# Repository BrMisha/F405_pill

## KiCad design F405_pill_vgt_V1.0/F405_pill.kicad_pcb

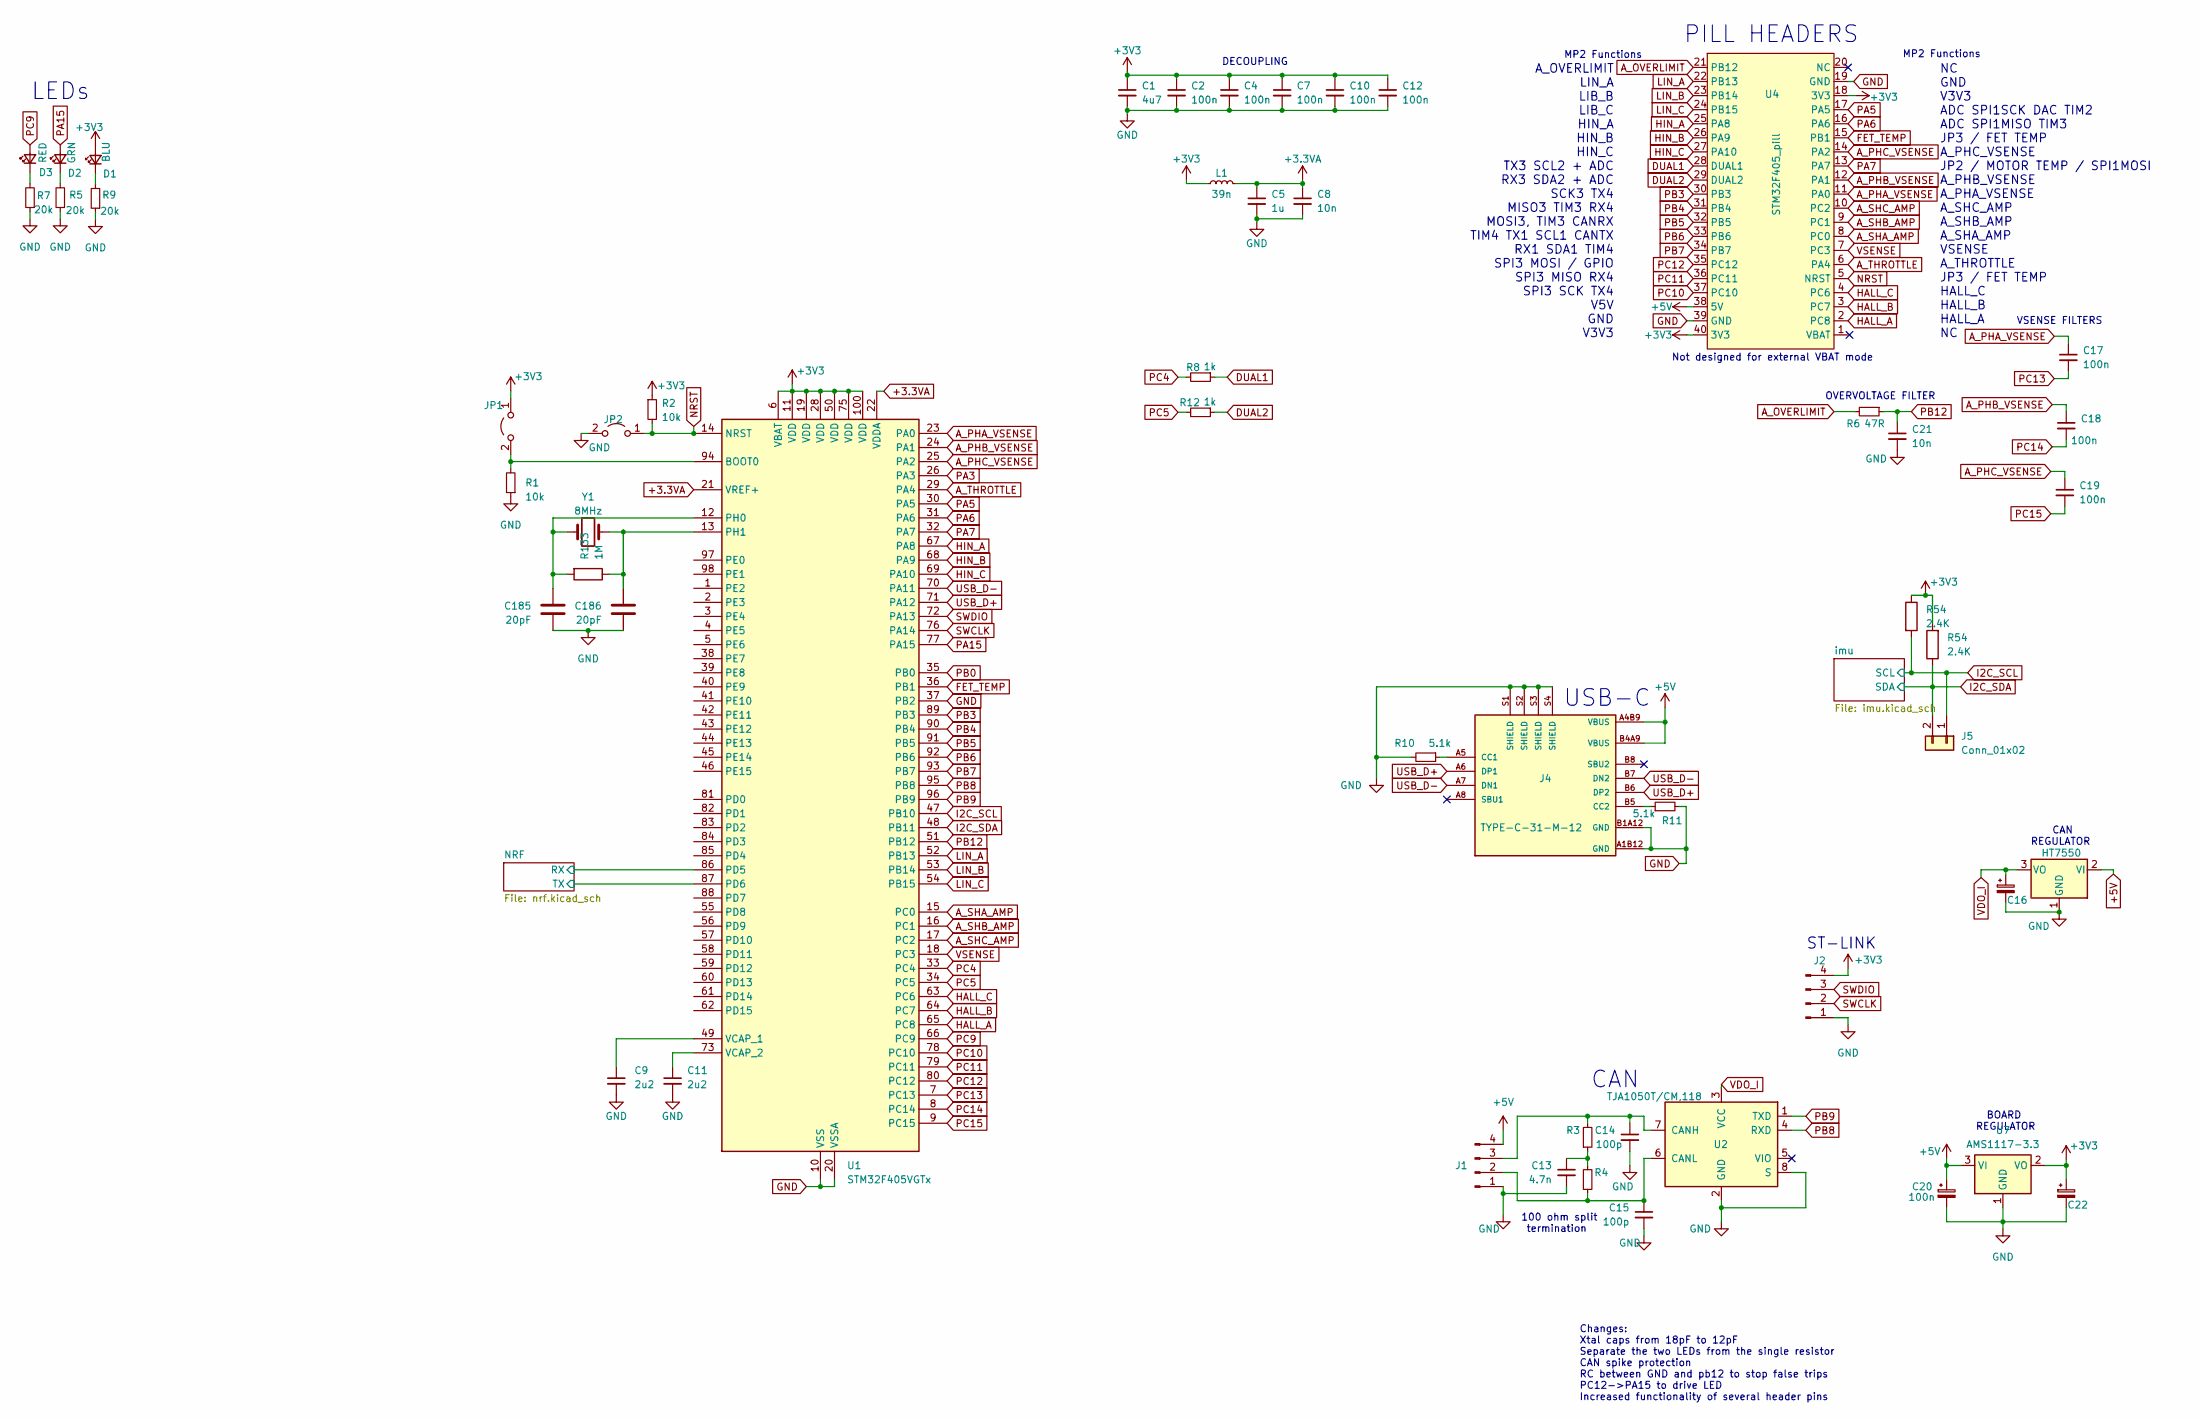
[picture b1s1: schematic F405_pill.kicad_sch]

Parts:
C1: 4u7; C_0402_1005Metric; LCSC C23733
C2, C4, C7, C10, C12, C17, C18, C19: 100n; C_0402_1005Metric; LCSC C1525
C5: 1u; C_0402_1005Metric; LCSC C52923
C8, C21: 10n; C_0402_1005Metric; LCSC C15195
C9, C11: 2u2; C_0603_1608Metric; LCSC C23630
C13: 4.7n; C_0402_1005Metric; LCSC C1538
C14, C15: 100p; C_0402_1005Metric; LCSC C1546
C16, C22: 10u; C_0603_1608Metric; LCSC C962635
C20: 100n; CP_EIA-3216-18_Kemet-A; LCSC C122257
C185, C186: 20pF; C_0402_1005Metric; MPN C1554
D1: BLU; LED_0603_1608Metric; LCSC C72041
D2: GRN; LED_0603_1608Metric; LCSC C72043
D3: RED; LED_0603_1608Metric; LCSC C2286
J1, J2: Conn_01x04_Male; my_4_pin
J4: TYPE-C-31-M-12; HRO_TYPE-C-31-M-12; PARTREV A; LCSC C165948
J5: Conn_01x02; PinHeader_1x02_P2.54mm_Vertical
JP1, JP2: Jumper_2_Open; my_2_pin
L1: 39n; L_0402_1005Metric; LCSC C26443
R1, R2: 10k; R_0402_1005Metric; LCSC C25744
R3, R4: 100Ω; R_0402_1005Metric; LCSC C25076
R5, R7, R9: 20k; R_0402_1005Metric; LCSC C25765
R6: 47R; R_0402_1005Metric; LCSC C25118
R8, R12: 1k; R_0402_1005Metric; LCSC C11702
R10, R11: 5.1k; R_0402_1005Metric; LCSC C25905
R54: 2.4K; R_0805_2012Metric; MPN C17526
R133: 1M; R_0402_1005Metric; MPN C26083
U1: STM32F405VGTx; LQFP-100_14x14mm_P0.5mm; LCSC C56621
U2: TJA1050T/CM,118; SOIC-8_3.9x4.9mm_P1.27mm; LCSC C6952
U4: STM32F405_pill
U5: HT7550; SOT-89-3; LCSC C16106
U7: AMS1117-3.3; SOT-223-3_TabPin2; MPN C6186
Y1: 8MHz; Crystal_SMD_5032-2Pin_5.0x3.2mm; MPN C115962

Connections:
+3.3VA: C5.1, C8.1, L1.2, U1.21 (VREF+), U1.22 (VDDA)
+3V3: C1.1, C2.1, C4.1, C7.1, C10.1, C12.1, C22.1, D1.2 (A), J2.4, JP1.1 (A), L1.1, R2.1, U1.6 (VBAT), U1.11 (VDD), U1.19 (VDD), U1.28 (VDD), U1.50 (VDD), U1.75 (VDD), U1.100 (VDD), U4.18 (3V3), U4.40 (3V3), U7.2 (VO); also elsewhere on the board
+5V: C20.1, J1.4, J4.A4B9 (VBUS), J4.B4A9 (VBUS), U4.38 (5V), U5.2 (VI), U7.3 (VI)
/NRF/RX: U1.86 (PD5); also elsewhere on the board
/NRF/TX: U1.87 (PD6); also elsewhere on the board
A_OVERLIMIT: R6.2, U4.21 (PB12)
A_PHA_VSENSE: C17.1, U1.23 (PA0), U4.11 (PA0)
A_PHB_VSENSE: C18.1, U1.24 (PA1), U4.12 (PA1)
A_PHC_VSENSE: C19.1, U1.25 (PA2), U4.14 (PA2)
A_SHA_AMP: U1.15 (PC0), U4.8 (PC0)
A_SHB_AMP: U1.16 (PC1), U4.9 (PC1)
A_SHC_AMP: U1.17 (PC2), U4.10 (PC2)
A_THROTTLE: U1.29 (PA4), U4.6 (PA4)
DUAL1: R8.1, U4.28 (DUAL1)
DUAL2: R12.1, U4.29 (DUAL2)
FET_TEMP: U1.36 (PB1), U4.15 (PB1)
GND: C1.2, C2.2, C4.2, C5.2, C7.2, C8.2, C9.2, C10.2, C11.2, C12.2, C13.2, C14.2, C15.2, C16.2, C20.2, C21.2, C22.2, J1.1, J2.1, J4.A1B12 (GND), J4.B1A12 (GND), J4.S1 (SHIELD), J4.S2 (SHIELD), J4.S3 (SHIELD), J4.S4 (SHIELD), JP2.2 (B), R1.1, R5.1, R7.1, R9.1, R10.2, R11.2, U1.10 (VSS), U1.20 (VSSA), U1.27 (VSS), U1.37 (PB2), U1.74 (VSS), U1.99 (VSS), U2.2 (GND), U2.8 (S), U4.19 (GND), U4.39 (GND), U5.1 (GND), U7.1 (GND); also elsewhere on the board
HALL_A: U1.65 (PC8), U4.2 (PC8)
HALL_B: U1.64 (PC7), U4.3 (PC7)
HALL_C: U1.63 (PC6), U4.4 (PC6)
HIN_A: U1.67 (PA8), U4.25 (PA8)
HIN_B: U1.68 (PA9), U4.26 (PA9)
HIN_C: U1.69 (PA10), U4.27 (PA10)
I2C_SCL: J5.1, U1.47 (PB10); also elsewhere on the board
I2C_SDA: J5.2, U1.48 (PB11); also elsewhere on the board
LIN_A: U1.52 (PB13), U4.22 (PB13)
LIN_B: U1.53 (PB14), U4.23 (PB14)
LIN_C: U1.54 (PB15), U4.24 (PB15)
NRST: JP2.1 (A), R2.2, U1.14 (NRST), U4.5 (NRST)
unnamed: C13.1, R3.1, R4.2
unnamed: D1.1 (K), R9.2
unnamed: D2.1 (K), R5.2
unnamed: D3.1 (K), R7.2
unnamed: C15.1, J1.2, R4.1, U2.6 (CANL)
unnamed: C14.1, J1.3, R3.2, U2.7 (CANH)
unnamed: J4.A5 (CC1), R10.1
unnamed: J4.B5 (CC2), R11.1
unnamed: JP1.2 (B), R1.2, U1.94 (BOOT0)
unnamed 41: U1.12 (PH0), Y1.1; also elsewhere on the board
unnamed 42: U1.13 (PH1), Y1.2; also elsewhere on the board
unnamed: C9.1, U1.49 (VCAP_1)
unnamed: C11.1, U1.73 (VCAP_2)
PA3: U1.26 (PA3)
PA5: U1.30 (PA5), U4.17 (PA5)
PA6: U1.31 (PA6), U4.16 (PA6)
PA7: U1.32 (PA7), U4.13 (PA7)
PA15: D2.2 (A), U1.77 (PA15)
PB0: U1.35 (PB0)
PB3: U1.89 (PB3), U4.30 (PB3)
PB4: U1.90 (PB4), U4.31 (PB4)
PB5: U1.91 (PB5), U4.32 (PB5)
PB6: U1.92 (PB6), U4.33 (PB6)
PB7: U1.93 (PB7), U4.34 (PB7)
PB8: U1.95 (PB8), U2.4 (RXD)
PB9: U1.96 (PB9), U2.1 (TXD)
PB12: C21.1, R6.1, U1.51 (PB12)
PC4: R8.2, U1.33 (PC4)
PC5: R12.2, U1.34 (PC5)
PC9: D3.2 (A), U1.66 (PC9)
PC10: U1.78 (PC10), U4.37 (PC10)
PC11: U1.79 (PC11), U4.36 (PC11)
PC12: U1.80 (PC12), U4.35 (PC12)
PC13: C17.2, U1.7 (PC13)
PC14: C18.2, U1.8 (PC14)
PC15: C19.2, U1.9 (PC15)
SWCLK: J2.2, U1.76 (PA14)
SWDIO: J2.3, U1.72 (PA13)
USB_D+: J4.A6 (DP1), J4.B6 (DP2), U1.71 (PA12)
USB_D-: J4.A7 (DN1), J4.B7 (DN2), U1.70 (PA11)
VDO_I: C16.1, U2.3 (VCC), U5.3 (VO)
VSENSE: U1.18 (PC3), U4.7 (PC3)

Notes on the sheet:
CAN
NC GND V3V3 ADC SPI1SCK DAC TIM2 ADC SPI1MISO TIM3 JP3 / FET TEMP A_PHC_VSENSE JP2 / MOTOR TEMP / SPI1MOSI A_PHB_VSENSE A_PHA_VSENSE A_SHC_AMP A_SHB_AMP A_SHA_AMP VSENSE A_THROTTLE JP3 / FET TEMP HALL_C HALL_B HALL_A NC
ST-LINK
Changes: Xtal caps from 18pF to 12pF Separate the two LEDs from the single resistor CAN spike protection RC between GND and pb12 to stop false trips PC12->PA15 to drive LED Increased functionality of several header pins
A_OVERLIMIT LIN_A LIB_B LIB_C HIN_A HIN_B HIN_C TX3 SCL2 + ADC RX3 SDA2 + ADC SCK3 TX4 MISO3 TIM3 RX4 MOSI3, TIM3 CANRX TIM4 TX1 SCL1 CANTX RX1 SDA1 TIM4 SPI3 MOSI / GPIO SPI3 MISO RX4 SPI3 SCK TX4 V5V GND V3V3
BOARD REGULATOR
PILL HEADERS
MP2 Functions
CAN REGULATOR
VSENSE FILTERS
OVERVOLTAGE FILTER
LEDs
USB-C
Not designed for external VBAT mode
DECOUPLING
100 ohm split termination

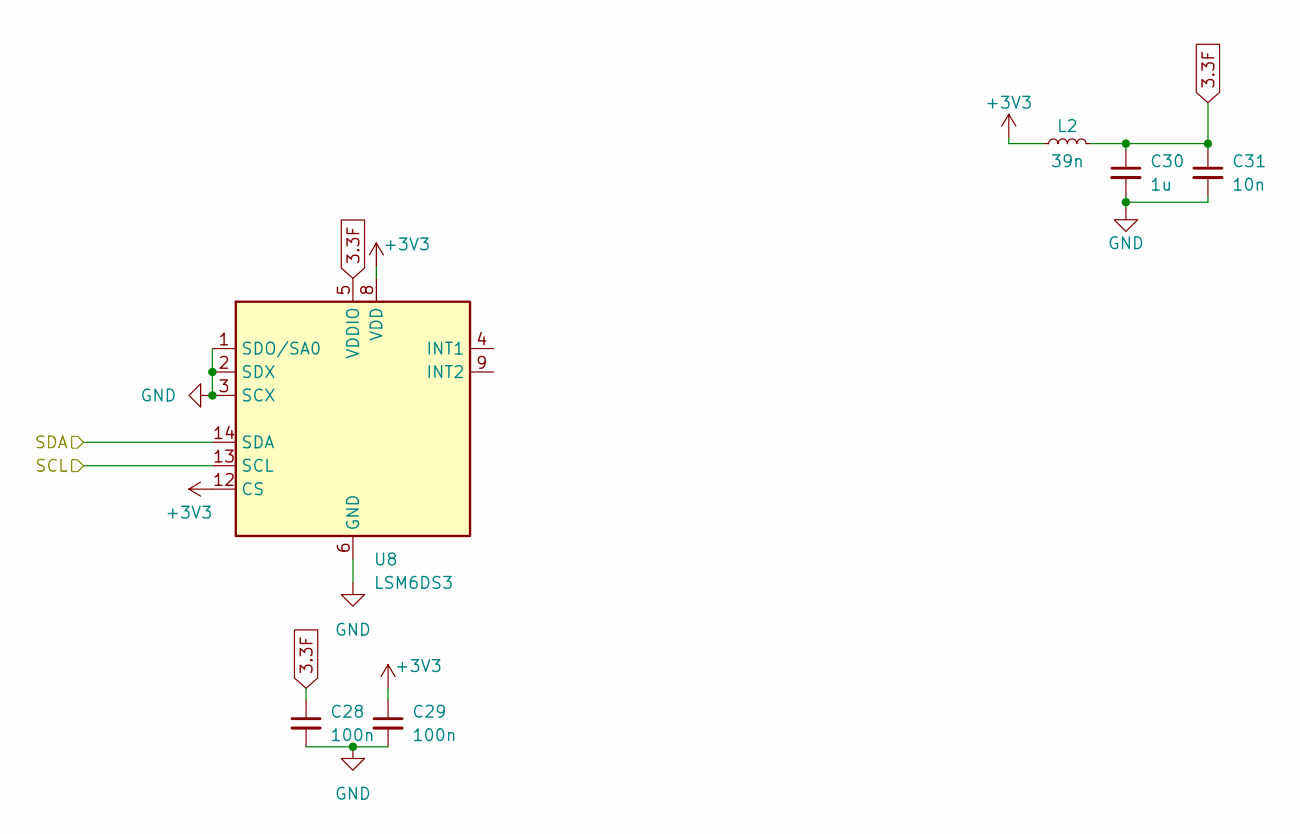
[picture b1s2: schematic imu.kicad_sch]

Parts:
C28, C29: 100n; C_0402_1005Metric; LCSC C1525
C30: 1u; C_0402_1005Metric; LCSC C52923
C31: 10n; C_0402_1005Metric; LCSC C15195
L2: 39n; L_0402_1005Metric; LCSC C26443
U8: LSM6DS3; LGA-14_3x2.5mm_P0.5mm_LayoutBorder3x4y; MPN C95230

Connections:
3.3F: C28.1, C30.1, C31.1, L2.2, U8.5 (VDDIO)
+3V3: C29.1, L2.1, U8.8 (VDD), U8.12 (CS); also elsewhere on the board
GND: C28.2, C29.2, C30.2, C31.2, U8.1 (SDO/SA0), U8.2 (SDX), U8.3 (SCX), U8.6 (GND), U8.7 (GND); also elsewhere on the board
I2C_SCL: U8.13 (SCL); also elsewhere on the board
I2C_SDA: U8.14 (SDA); also elsewhere on the board

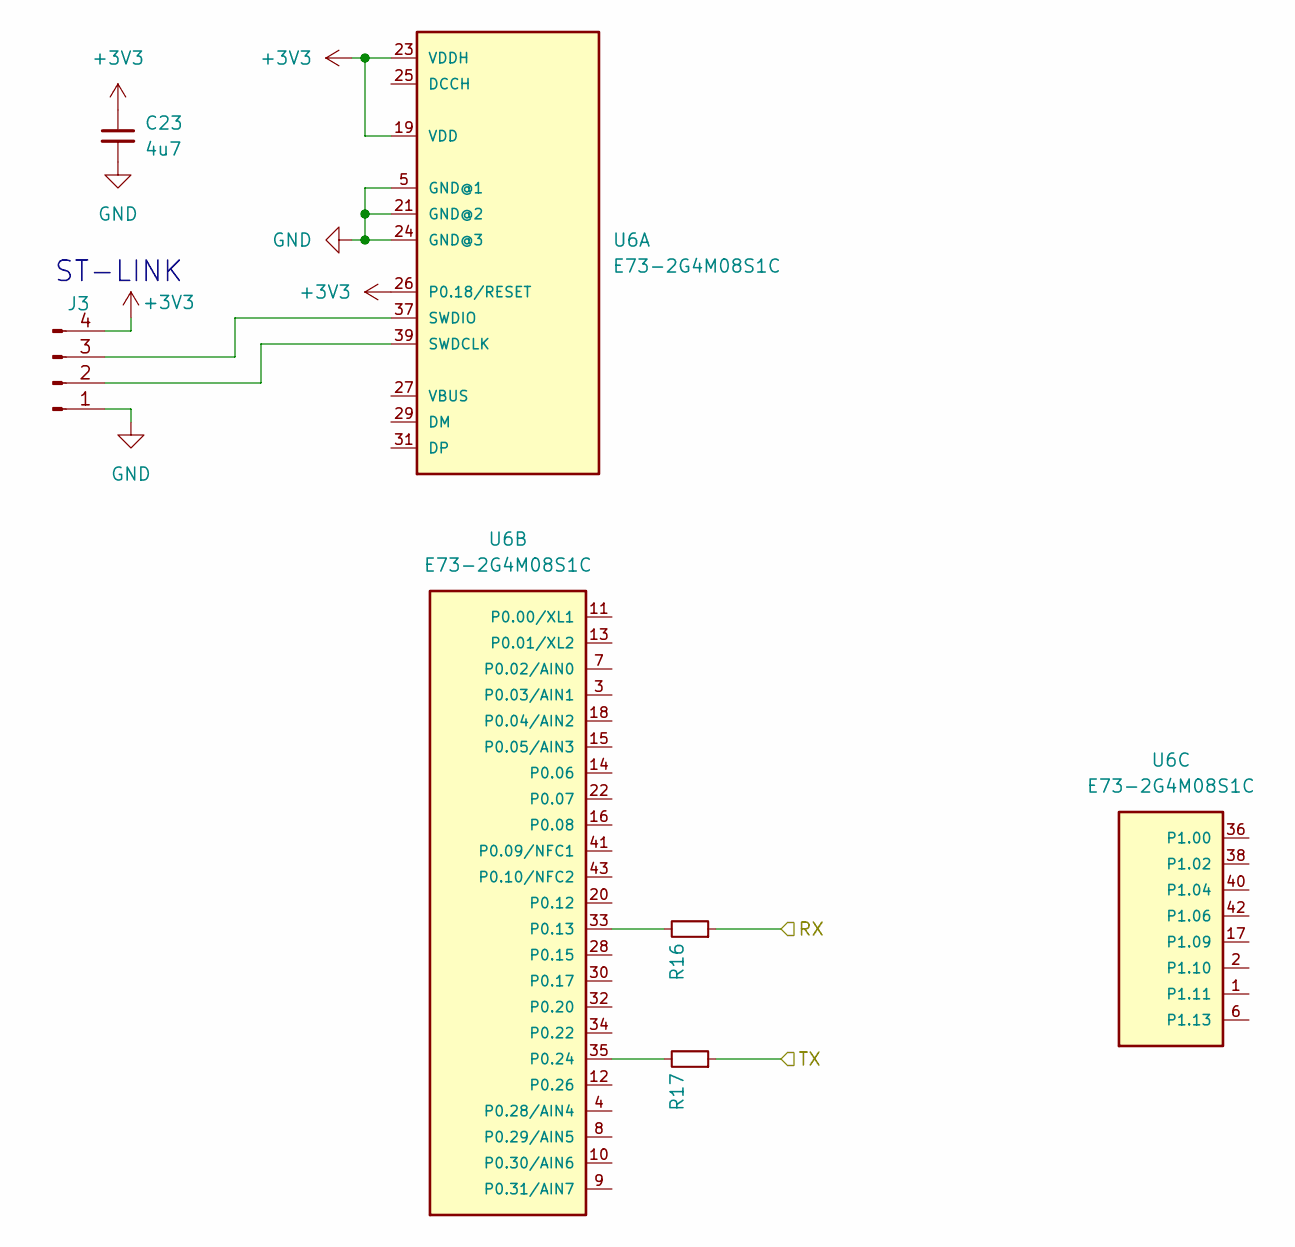
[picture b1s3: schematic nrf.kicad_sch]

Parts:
C23: 4u7; C_0402_1005Metric; LCSC C23733
J3: Conn_01x04_Male; PinHeader_1x04_P2.54mm_Vertical
R16, R17: 100Ω; R_0402_1005Metric; LCSC C25076
U6: E73-2G4M08S1C

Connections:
+3V3: C23.1, J3.4, U6.19 (VDD), U6.23 (VDDH), U6.26 (P0.18/RESET); also elsewhere on the board
/NRF/RX: R16.1; also elsewhere on the board
/NRF/TX: R17.1; also elsewhere on the board
GND: C23.2, J3.1, U6.5 (GND@1), U6.21 (GND@2), U6.24 (GND@3); also elsewhere on the board
unnamed: J3.2, U6.39 (SWDCLK)
unnamed: J3.3, U6.37 (SWDIO)
unnamed: R16.2, U6.33 (P0.13)
unnamed: R17.2, U6.35 (P0.24)

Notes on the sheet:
ST-LINK

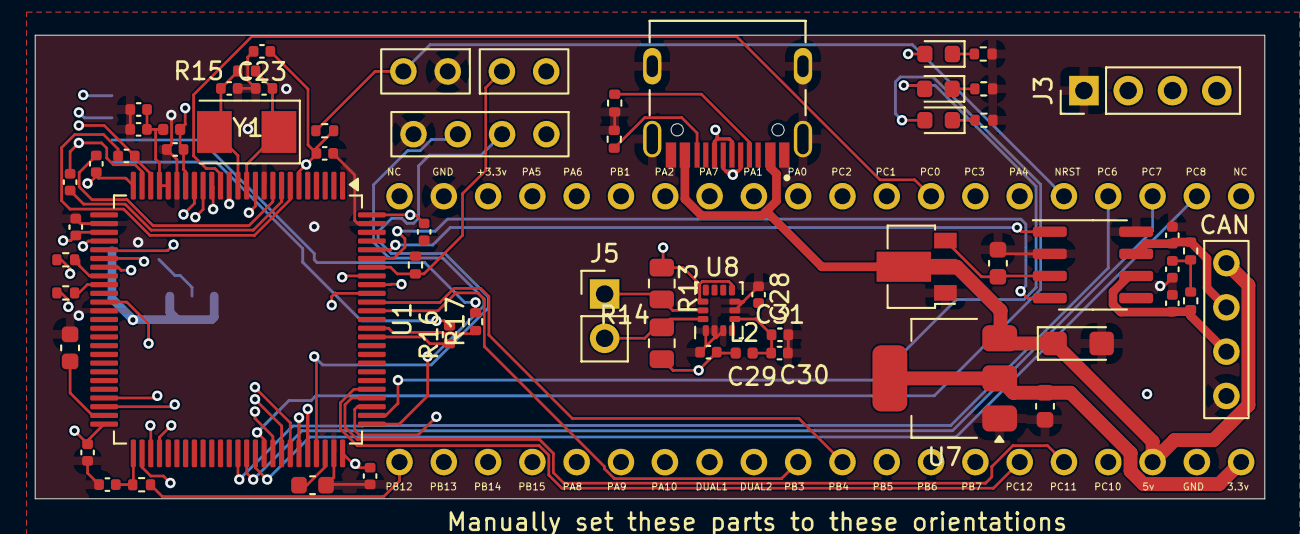
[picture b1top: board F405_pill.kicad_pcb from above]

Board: 4 copper layers, 70.5 x 26.6 mm, 64 parts (1 on the bottom side), 74 nets.

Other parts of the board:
C3, C6: 20pF; C_0402_1005Metric
R13, R14: 2.4K; R_0805_2012Metric
R15: 1M; R_0402_1005Metric

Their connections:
+3V3: R13.1, R14.2; also elsewhere on the board
GND: C3.1, C6.1; also elsewhere on the board
I2C_SCL: R13.2; also elsewhere on the board
I2C_SDA: R14.1; also elsewhere on the board
unnamed 41: C3.2, R15.2; also elsewhere on the board
unnamed 42: C6.2, R15.1; also elsewhere on the board

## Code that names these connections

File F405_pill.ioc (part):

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Mcu.Name=STM32F405VGTx
Mcu.Package=LQFP100
Mcu.UserName=STM32F405VGTx
PA0-WKUP.GPIOParameters=GPIO_Label
PA0-WKUP.GPIO_Label=A_PHA_VSENSE
PA0-WKUP.Signal=GPIO_Input
PA1.GPIOParameters=GPIO_Label
PA1.GPIO_Label=A_PHB_VSENSE
PA1.Signal=GPIO_Input
PA10.GPIOParameters=GPIO_Label
PA10.GPIO_Label=HIN_C
PA10.Signal=GPIO_Output
PA11.Mode=Device_Only
PA11.Signal=USB_OTG_FS_DM
PA12.Mode=Device_Only
PA12.Signal=USB_OTG_FS_DP
PA2.GPIOParameters=GPIO_Label
PA2.GPIO_Label=A_PHC_VSENSE
PA2.Signal=GPIO_Input
PA4.GPIOParameters=GPIO_Label
PA4.GPIO_Label=A_THROTTLE
PA4.Signal=GPIO_Analog
PA8.GPIOParameters=GPIO_Label
PA8.GPIO_Label=HIN_A
PA8.Signal=GPIO_Output
PA9.GPIOParameters=GPIO_Label
PA9.GPIO_Label=HIN_B
PA9.Signal=GPIO_Output
PB1.GPIOParameters=GPIO_Label
PB1.GPIO_Label=FET_TEMP
PB1.Signal=GPIO_Analog
PB10.Mode=I2C
PB10.Signal=I2C2_SCL
PB11.Mode=I2C
PB11.Signal=I2C2_SDA
PB12.GPIOParameters=GPIO_Label
PB12.GPIO_Label=A_OVERLIMIT
PB12.Signal=GPIO_Analog
PB13.GPIOParameters=GPIO_Label
PB13.GPIO_Label=LIN_A
PB13.Signal=GPIO_Output
PB14.GPIOParameters=GPIO_Label
PB14.GPIO_Label=LIN_B
PB14.Signal=GPIO_Output
PB15.GPIOParameters=GPIO_Label
PB15.GPIO_Label=LIN_C
PB15.Signal=GPIO_Output
PC0.GPIOParameters=GPIO_Label
PC0.GPIO_Label=A_SHA_AMP
PC0.Signal=GPIO_Analog
PC1.GPIOParameters=GPIO_Label
PC1.GPIO_Label=A_SHB_AMP
PC1.Signal=GPIO_Analog
PC10.Mode=Asynchronous
PC10.Signal=USART3_TX
PC11.Mode=Asynchronous
PC11.Signal=USART3_RX
PC2.GPIOParameters=GPIO_Label
PC2.GPIO_Label=A_SHC_AMP
PC2.Signal=GPIO_Analog
PC3.GPIOParameters=GPIO_Label
PC3.GPIO_Label=VSENSE
PC3.Signal=GPIO_Analog
PC6.GPIOParameters=GPIO_Label
PC6.GPIO_Label=HALL_C
PC6.Signal=GPIO_Input
PC7.GPIOParameters=GPIO_Label
PC7.GPIO_Label=HALL_B
PC7.Signal=GPIO_Input
PC8.GPIOParameters=GPIO_Label
PC8.GPIO_Label=HALL_A
PC8.Signal=GPIO_Input
PD5.GPIOParameters=GPIO_Label
PD5.GPIO_Label=NRF_TX
PD5.Mode=Asynchronous
PD5.Signal=USART2_TX
PD6.GPIOParameters=GPIO_Label
PD6.GPIO_Label=NRF_RX
PD6.Mode=Asynchronous
PD6.Signal=USART2_RX
RCC.HSE_VALUE=25000000
RCC.SYSCLKFreq_VALUE=16000000
board=custom

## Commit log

2023-09-12 add imu
2023-09-12 removed one imu
2023-09-12 add bmi270
2023-09-12 fixed for prodaction
2024-11-15 add MCU
2024-11-16 add E73
2024-11-16 Schematic is finished
2024-11-16 Rarticly routed
2024-11-16 pcb finished
2025-01-16 Fixed pin
2025-01-16 updated for prodaction
2025-02-10 moved
2025-02-10 add old version
2025-03-02 add headers
2025-03-03 add readme
2025-03-04 fixed usart
2025-05-10 rised current
2025-06-06 updated current
